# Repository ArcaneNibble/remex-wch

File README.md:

# Project codename "remex"

> remex (noun)
>> a primary or secondary quill feather of the wing of a bird

This is intended to be a "maker"-friendly board for the CH32V307 RISC-V microcontroller from [WCH](https://www.wch-ic.com/). The main selling points are gigabit Ethernet and USB-C including host support.

## Status

There's a vaguely-complete layout, but actual ordering is pending final schematic review as well as further stress-testing of the chosen LiPo charger circuitry.

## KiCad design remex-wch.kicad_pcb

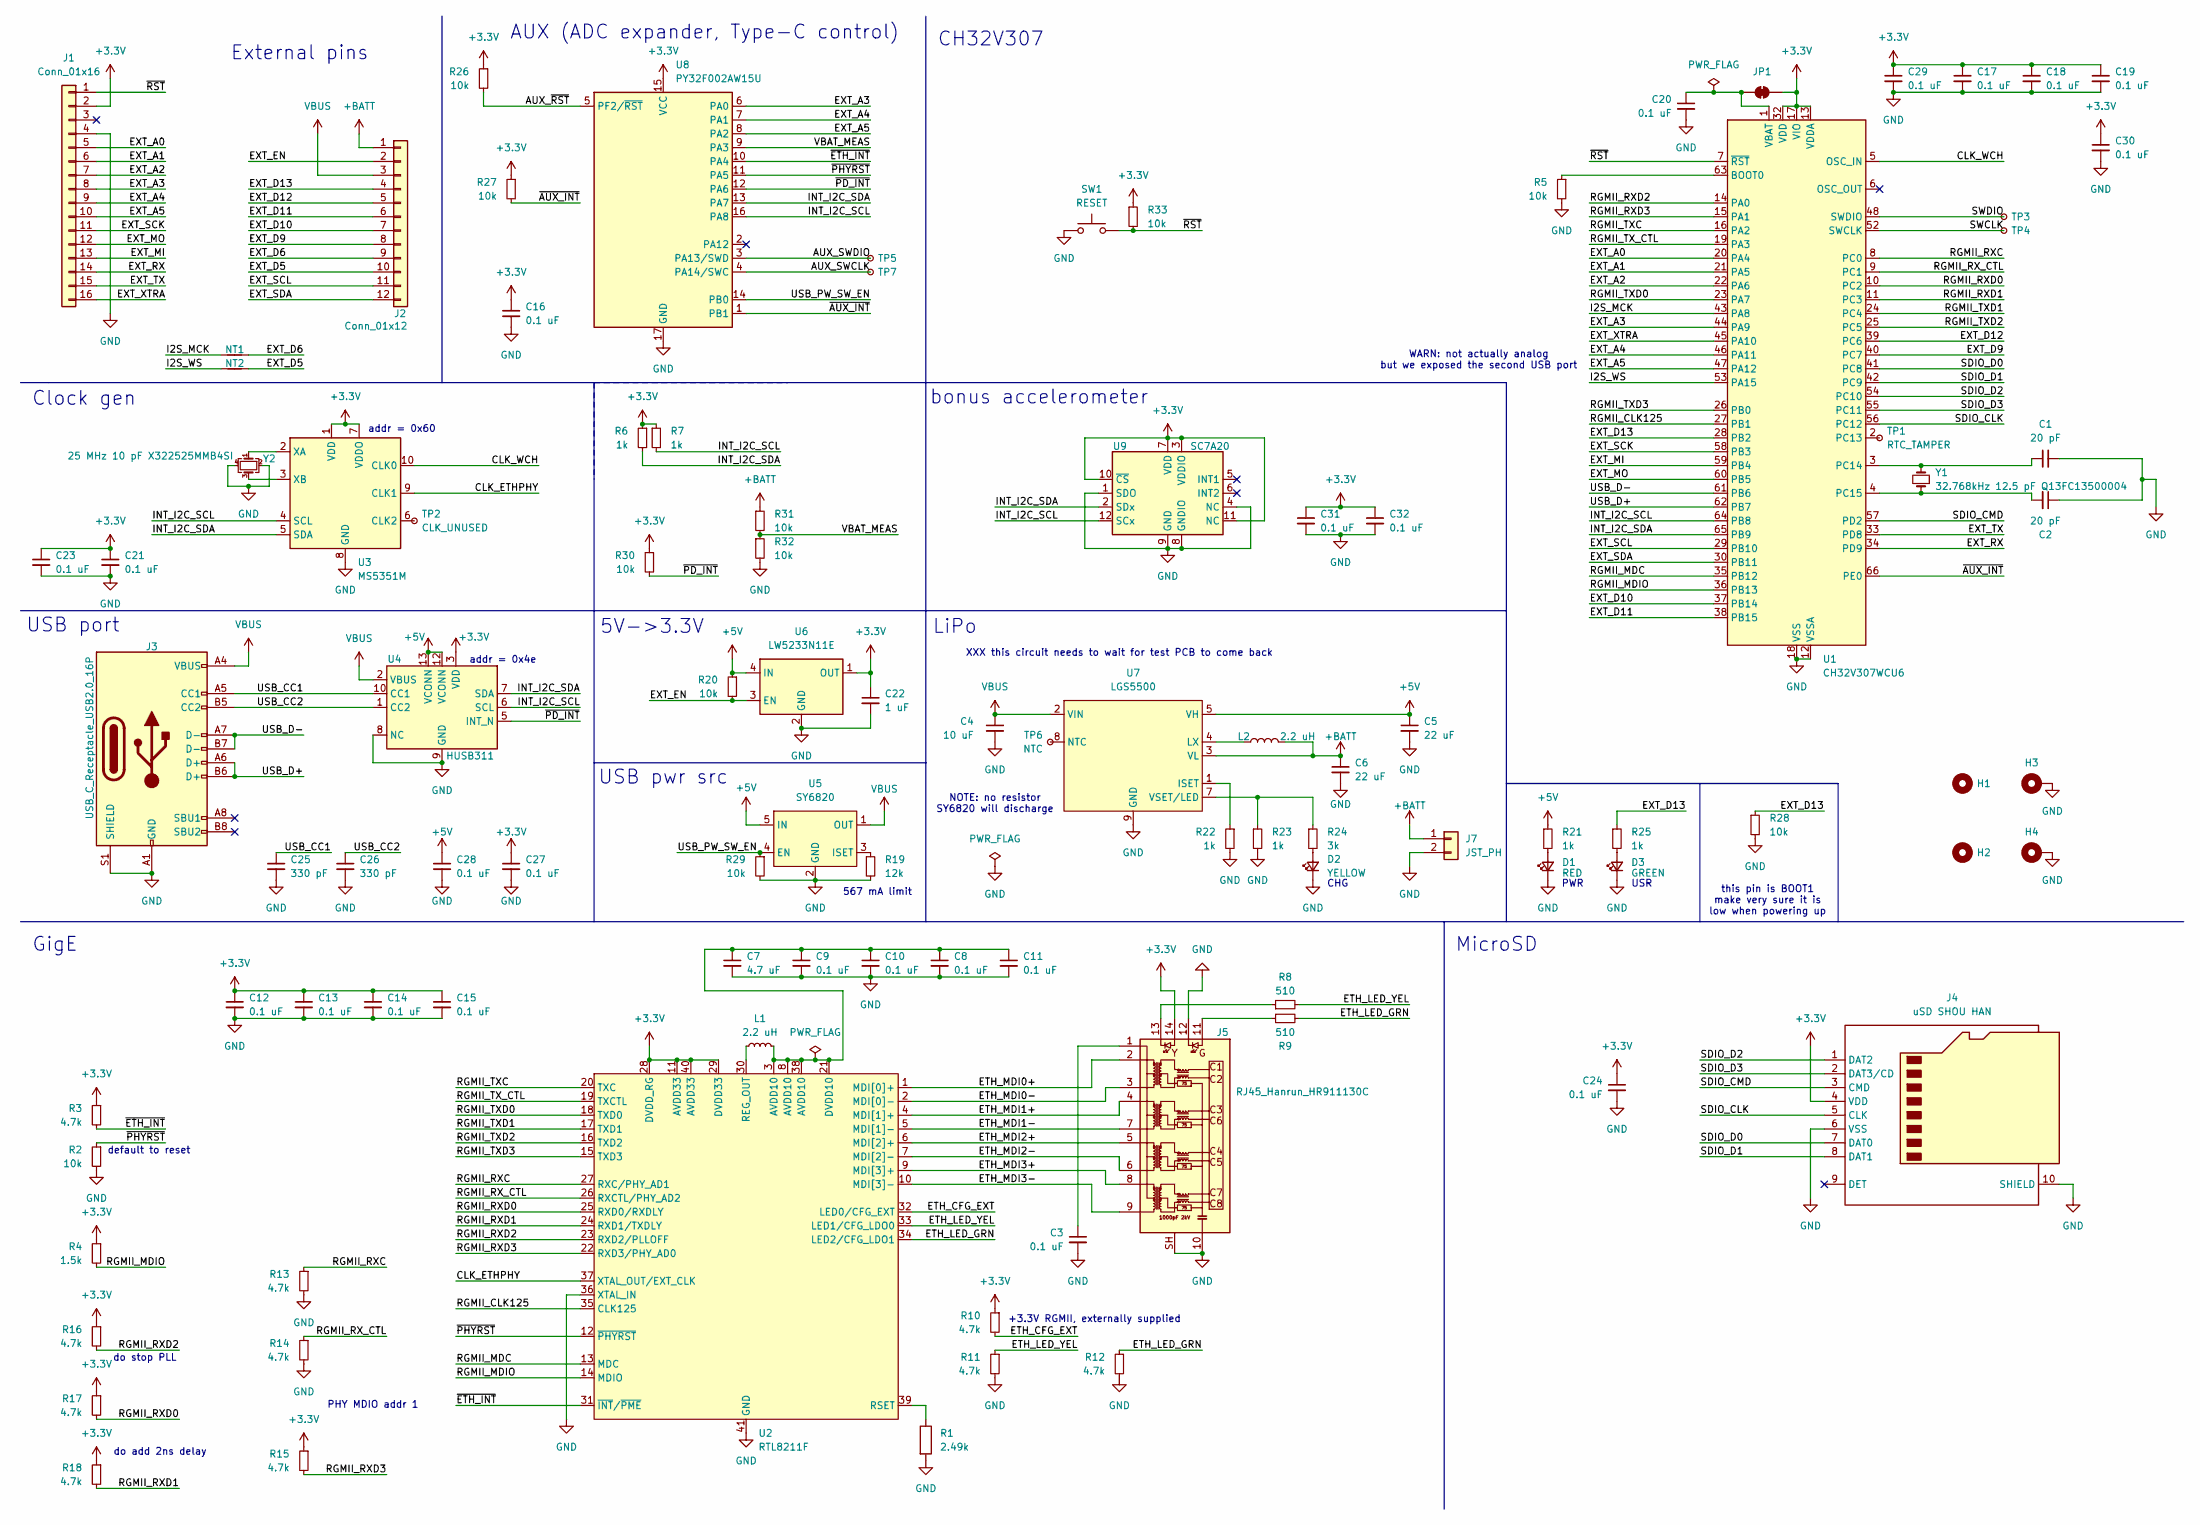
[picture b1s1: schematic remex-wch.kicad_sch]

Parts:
C1, C2: 20 pF; C_0402_1005Metric; LCSC C1554
C3, C8, C9, C10, C11, C12, C13, C14, C15, C16, C17, C18, C19, C20, C21, C23, C24, C27, C28, C29, C30, C31, C32: 0.1 uF; C_0402_1005Metric; LCSC C1525
C4: 10 uF; C_1206_3216Metric; LCSC C13585
C5, C6: 22 uF; C_1206_3216Metric; LCSC C12891
C7: 4.7 uF; C_0603_1608Metric; LCSC C19666
C22: 1 uF; C_0603_1608Metric; LCSC C15849
C25, C26: 330 pF; C_0402_1005Metric; LCSC C13533
D1: RED; LED_0603_1608Metric; LCSC C2286
D2: YELLOW; LED_0603_1608Metric; LCSC C72038
D3: GREEN; LED_0603_1608Metric; LCSC C965804
H1, H2: MountingHole; MountingHole_2.5mm
H3, H4: MountingHole_Pad; MountingHole_2.5mm_Pad
J1: Conn_01x16; PinHeader_1x16_P2.54mm_Vertical
J2: Conn_01x12; PinHeader_1x12_P2.54mm_Vertical
J3: USB_C_Receptacle_USB2.0_16P; USB_C_Receptacle_GCT_USB4105-xx-A_16P_TopMnt_Horizontal; LCSC C2765186
J4: uSD SHOU HAN; microSD_SHOU_HAN_H1.8; LCSC C7529389
J5: RJ45_Hanrun_HR911130C; LCSC C50933
J7: JST_PH; JST_PH_S2B-PH-SM4-TB_1x02-1MP_P2.00mm_Horizontal; LCSC C295747
JP1: VBAT; SolderJumper-2_P1.3mm_Bridged_RoundedPad1.0x1.5mm
L1, L2: 2.2 uH; L_Changjiang_FXL0420; LCSC C167206
NT1, NT2: NetTie_2; nettie_tiny
R1: 2.49k; R_0402_1005Metric; LCSC C145071
R2, R5, R20, R26, R27, R28, R29, R30, R31, R32, R33: 10k; R_0402_1005Metric; LCSC C25744
R3, R10, R11, R12, R13, R14, R15, R16, R17, R18: 4.7k; R_0402_1005Metric; LCSC C25900
R4: 1.5k; R_0402_1005Metric; LCSC C25867
R6, R7, R21, R22, R23, R25: 1k; R_0402_1005Metric; LCSC C11702
R8, R9: 510; R_0402_1005Metric; LCSC C25123
R19: 12k; R_0402_1005Metric; LCSC C25752
R24: 3k; R_0603_1608Metric; LCSC C4211
SW1: RESET; SW_Push_1P1T_XKB_TS-1187A; LCSC C318884
TP1: RTC_TAMPER; TestPoint_Pad_1.0x1.0mm
TP2: CLK_UNUSED; TestPoint_Pad_1.0x1.0mm
TP3: SWDIO; TestPoint_Pad_1.0x1.0mm
TP4: SWCLK; TestPoint_Pad_1.0x1.0mm
TP5: AUX_SWDIO; TestPoint_Pad_1.0x1.0mm
TP6: NTC; TestPoint_Pad_1.0x1.0mm
TP7: AUX_SWCLK; TestPoint_Pad_1.0x1.0mm
U1: CH32V307WCU6; QFN-68-1EP_8x8mm_P0.4mm_EP6.4x6.4mm; LCSC C5142795
U2: RTL8211F; QFN-40-1EP_5x5mm_P0.4mm_EP3.7x3.7mm; LCSC C187932
U3: MS5351M; MSOP-10_3x3mm_P0.5mm; LCSC C1509083
U4: HUSB311; WQFN-14-1EP_2.5x2.5mm_P0.5mm_EP1.4x1.4mm; LCSC C7471922
U5: SY6820; SOT-23-5; LCSC C55136
U6: LW5233N11E; OnSemi_XDFN4-1EP_1.0x1.0mm_EP0.52x0.52mm; LCSC C20630430
U7: LGS5500; SOIC-8-1EP_3.9x4.9mm_P1.27mm_EP2.41x3.3mm; LCSC C5280699
U8: PY32F002AW15U; QFN-16-1EP_3x3mm_P0.5mm_EP1.7x1.7mm; LCSC C5291740
U9: SC7A20; LGA-12_2x2mm_P0.5mm
Y1: 32.768kHz 12.5 pF Q13FC13500004; Crystal_SMD_3215-2Pin_3.2x1.5mm; LCSC C32346
Y2: 25 MHz 10 pF X322525MMB4SI; Crystal_SMD_3225-4Pin_3.2x2.5mm; LCSC C70582

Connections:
+3.3V: C12.1, C13.1, C14.1, C15.1, C16.1, C17.1, C18.1, C19.1, C21.1, C22.1, C23.1, C24.1, C27.1, C29.1, C30.1, C31.1, C32.1, J1.2, J4.4 (VDD), J5.14, JP1.2 (B), R3.1, R4.1, R6.1, R7.1, R10.1, R15.1, R16.1, R17.1, R18.1, R26.1, R27.1, R30.1, R33.1, U1.13 (VDDA), U1.17 (VIO), U1.31 (VIO), U1.32 (VDD), U1.50 (VDD), U1.51 (VIO), U1.67 (VIO), U1.68 (VDD), U2.11 (AVDD33), U2.28 (DVDD_RG), U2.29 (DVDD33), U2.40 (AVDD33), U3.1 (VDD), U3.7 (VDDO), U4.3 (VDD), U4.4 (VDD), U6.1 (OUT), U8.15 (VCC), U9.3 (VDDIO), U9.7 (VDD), U9.10 (~CS), U9.11 (NC)
+5V: C5.1, C28.1, R20.1, R21.1, U4.12 (VCONN), U4.13 (VCONN), U5.5 (IN), U6.4 (IN), U7.5 (VH)
+BATT: C6.1, J2.1, J7.1, L2.2, R31.1, U7.3 (VL)
/AUX_SWCLK: TP7.1, U8.4 (PA14/SWC)
/AUX_SWDIO: TP5.1, U8.3 (PA13/SWD)
/AUX_~RST: R26.2, U8.5 (PF2/~RST)
/CLK_ETHPHY: U2.37 (XTAL_OUT/EXT_CLK), U3.9 (CLK1)
/CLK_WCH: U1.5 (OSC_IN), U3.10 (CLK0)
/ETH_CFG_EXT: R10.2, U2.32 (LED0/CFG_EXT)
/ETH_LED_GRN: R9.2, R12.1, U2.34 (LED2/CFG_LDO1)
/ETH_LED_YEL: R8.2, R11.1, U2.33 (LED1/CFG_LDO0)
/ETH_MDI0+: J5.2 (TD1+), U2.1 (MDI[0]+)
/ETH_MDI0-: J5.3 (TD1-), U2.2 (MDI[0]-)
/ETH_MDI1+: J5.4 (TD2+), U2.4 (MDI[1]+)
/ETH_MDI1-: J5.7 (TD2-), U2.5 (MDI[1]-)
/ETH_MDI2+: J5.5 (TD3+), U2.6 (MDI[2]+)
/ETH_MDI2-: J5.6 (TD3-), U2.7 (MDI[2]-)
/ETH_MDI3+: J5.8 (TD4+), U2.9 (MDI[3]+)
/ETH_MDI3-: J5.9 (TD4-), U2.10 (MDI[3]-)
/EXT_A0: J1.5, U1.20 (PA4)
/EXT_A1: J1.6, U1.21 (PA5)
/EXT_A2: J1.7, U1.22 (PA6)
/EXT_A3: J1.8, U1.44 (PA9), U8.6 (PA0)
/EXT_A4: J1.9, U1.46 (PA11), U8.7 (PA1)
/EXT_A5: J1.10, U1.47 (PA12), U8.8 (PA2)
/EXT_D5: J2.10, NT2.2
/EXT_D6: J2.9, NT1.2
/EXT_D9: J2.8, U1.40 (PC7)
/EXT_D10: J2.7, U1.37 (PB14)
/EXT_D11: J2.6, U1.38 (PB15)
/EXT_D12: J2.5, U1.39 (PC6)
/EXT_D13: J2.4, R25.1, R28.1, U1.28 (PB2)
/EXT_EN: J2.2, R20.2, U6.3 (EN)
/EXT_MI: J1.13, U1.59 (PB4)
/EXT_MO: J1.12, U1.60 (PB5)
/EXT_RX: J1.14, U1.34 (PD9)
/EXT_SCK: J1.11, U1.58 (PB3)
/EXT_SCL: J2.11, U1.29 (PB10)
/EXT_SDA: J2.12, U1.30 (PB11)
/EXT_TX: J1.15, U1.33 (PD8)
/EXT_XTRA: J1.16, U1.45 (PA10)
/I2S_MCK: NT1.1, U1.43 (PA8)
/I2S_WS: NT2.1, U1.53 (PA15)
/INT_I2C_SCL: R7.2, U1.64 (PB8), U3.4 (SCL), U4.6 (SCL), U8.16 (PA8), U9.12 (SCx)
/INT_I2C_SDA: R6.2, U1.65 (PB9), U3.5 (SDA), U4.7 (SDA), U8.13 (PA7), U9.2 (SDx)
/RGMII_CLK125: U1.27 (PB1), U2.35 (CLK125)
/RGMII_MDC: U1.35 (PB12), U2.13 (MDC)
/RGMII_MDIO: R4.2, U1.36 (PB13), U2.14 (MDIO)
/RGMII_RXC: R13.1, U1.8 (PC0), U2.27 (RXC/PHY_AD1)
/RGMII_RXD0: R17.2, U1.10 (PC2), U2.25 (RXD0/RXDLY)
/RGMII_RXD1: R18.2, U1.11 (PC3), U2.24 (RXD1/TXDLY)
/RGMII_RXD2: R16.2, U1.14 (PA0), U2.23 (RXD2/PLLOFF)
/RGMII_RXD3: R15.2, U1.15 (PA1), U2.22 (RXD3/PHY_AD0)
/RGMII_RX_CTL: R14.1, U1.9 (PC1), U2.26 (RXCTL/PHY_AD2)
/RGMII_TXC: U1.16 (PA2), U2.20 (TXC)
/RGMII_TXD0: U1.23 (PA7), U2.18 (TXD0)
/RGMII_TXD1: U1.24 (PC4), U2.17 (TXD1)
/RGMII_TXD2: U1.25 (PC5), U2.16 (TXD2)
/RGMII_TXD3: U1.26 (PB0), U2.15 (TXD3)
/RGMII_TX_CTL: U1.19 (PA3), U2.19 (TXCTL)
/SDIO_CLK: J4.5 (CLK), U1.56 (PC12)
/SDIO_CMD: J4.3 (CMD), U1.57 (PD2)
/SDIO_D0: J4.7 (DAT0), U1.41 (PC8)
/SDIO_D1: J4.8 (DAT1), U1.42 (PC9)
/SDIO_D2: J4.1 (DAT2), U1.54 (PC10)
/SDIO_D3: J4.2 (DAT3/CD), U1.55 (PC11)
/SWCLK: TP4.1, U1.52 (SWCLK)
/SWDIO: TP3.1, U1.48 (SWDIO)
/USB_CC1: C25.1, J3.A5 (CC1), U4.10 (CC1), U4.11 (CC1)
/USB_CC2: C26.1, J3.B5 (CC2), U4.1 (CC2), U4.14 (CC2)
/USB_D+: J3.A6 (D+), J3.B6 (D+), U1.62 (PB7)
/USB_D-: J3.A7 (D-), J3.B7 (D-), U1.61 (PB6)
/USB_PW_SW_EN: R29.1, U5.4 (EN), U8.14 (PB0)
/VBAT_MEAS: R31.2, R32.1, U8.9 (PA3)
/~AUX_INT: R27.2, U1.66 (PE0), U8.1 (PB1)
/~ETH_INT: R3.2, U2.31 (~INT/~PME), U8.10 (PA4)
/~PD_INT: R30.2, U4.5 (INT_N), U8.12 (PA6)
/~PHYRST: R2.1, U2.12 (~PHYRST), U8.11 (PA5)
/~RST: J1.1, R33.2, SW1.2, U1.7 (~RST)
GND: C1.2, C2.1, C3.2, C4.2, C5.2, C6.2, C7.2, C8.2, C9.2, C10.2, C11.2, C12.2, C13.2, C14.2, C15.2, C16.2, C17.2, C18.2, C19.2, C20.2, C21.2, C22.2, C23.2, C24.2, C25.2, C26.2, C27.2, C28.2, C29.2, C30.2, C31.2, C32.2, D1.1 (K), D2.1 (K), D3.1 (K), H3.1, H4.1, J1.4, J3.A1 (GND), J3.A12 (GND), J3.B1 (GND), J3.B12 (GND), J3.S1 (SHIELD), J4.6 (VSS), J4.10 (SHIELD), J5.10 (GND), J5.12, J5.SH, J7.2, R1.2, R2.2, R5.2, R11.2, R12.2, R13.2, R14.2, R19.2, R22.2, R23.2, R28.2, R29.2, R32.2, SW1.1, U1.12 (VSSA), U1.18 (VSS), U1.49 (VSS), U1.69 (VSS), U2.36 (XTAL_IN), U2.41 (GND), U3.8 (GND), U4.8 (NC), U4.9 (GND), U4.15 (GND), U5.2 (GND), U6.2 (GND), U6.5 (GND), U7.9 (GND), U8.17 (GND), U9.1 (SDO), U9.4 (NC), U9.8 (GNDIO), U9.9 (GND), Y2.2, Y2.4
unnamed: D1.2 (A), R21.2
unnamed: D2.2 (A), R24.2
unnamed: D3.2 (A), R25.2
unnamed: C3.1, J5.1 (CT)
unnamed: J5.11, R9.1
unnamed: J5.13, R8.1
unnamed: C20.1, JP1.1 (A), U1.1 (VBAT)
unnamed: R5.1, U1.63 (BOOT0)
unnamed: TP1.1, U1.2 (PC13)
unnamed: C1.1, U1.3 (PC14), Y1.2
unnamed: C2.2, U1.4 (PC15), Y1.1
unnamed: C7.1, C8.1, C9.1, C10.1, C11.1, L1.2, U2.3 (AVDD10), U2.8 (AVDD10), U2.21 (DVDD10), U2.38 (AVDD10)
unnamed: L1.1, U2.30 (REG_OUT)
unnamed: R1.1, U2.39 (RSET)
unnamed: TP2.1, U3.6 (CLK2)
unnamed: U3.2 (XA), Y2.1
unnamed: U3.3 (XB), Y2.3
unnamed: R19.1, U5.3 (ISET)
unnamed: R22.1, U7.1 (ISET)
unnamed: L2.1, U7.4 (LX)
unnamed: TP6.1, U7.8 (NTC)
unnamed: R23.1, R24.1, U7.7 (VSET/LED)
VBUS: C4.1, J2.3, J3.A4 (VBUS), J3.A9 (VBUS), J3.B4 (VBUS), J3.B9 (VBUS), U4.2 (VBUS), U5.1 (OUT), U7.2 (VIN)

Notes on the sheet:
PWR
USB pwr src
USR
5V->3.3V
AUX (ADC expander, Type-C control)
USB port
MicroSD
CH32V307
GigE
default to reset
WARN: not actually analog but we exposed the second USB port
NOTE: no resistor SY6820 will discharge
LiPo
addr = 0x60
Clock gen
567 mA limit
CHG
External pins
this pin is BOOT1 make very sure it is low when powering up
do stop PLL
+3.3V RGMII, externally supplied
PHY MDIO addr 1
addr = 0x4e
bonus accelerometer
do add 2ns delay
XXX this circuit needs to wait for test PCB to come back

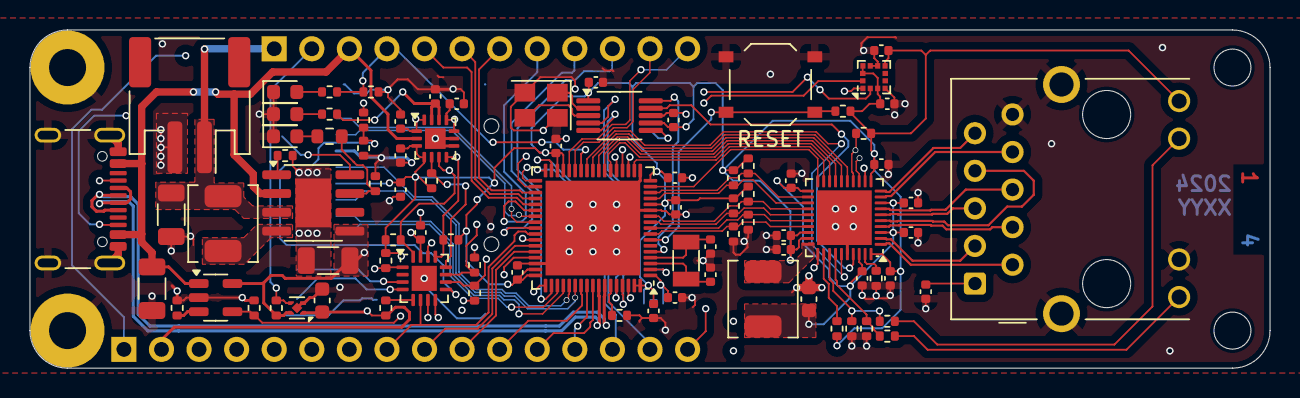
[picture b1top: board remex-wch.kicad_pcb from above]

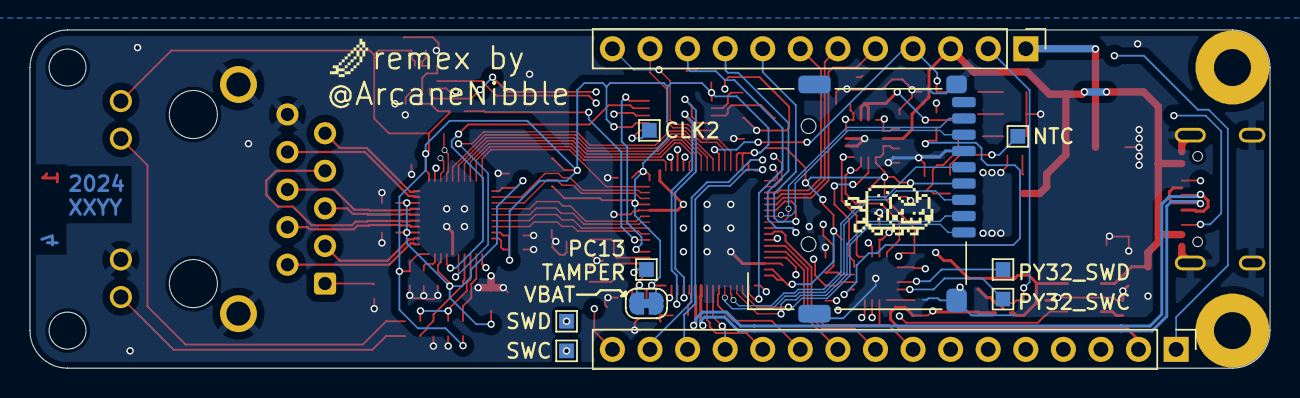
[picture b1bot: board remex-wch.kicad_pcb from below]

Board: 4 copper layers, 83.8 x 22.9 mm, 102 parts (13 on the bottom side), 103 nets.

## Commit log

2024-08-19 Initial pin allocation for MCU
2024-08-19 USB port; assign BOM data now
2024-08-19 Shuffle pins to get an internal I2C bus
2024-08-19 initial eth phy
2024-08-19 microsd socket
2024-08-19 clock generator
2024-08-19 ethernet magjack; straps
2024-08-19 rearrange positions
2024-08-19 misc
2024-08-19 add usb typec controller
2024-08-20 Add TBD LiPo circuitry
2024-08-20 py32 as io/adc expander and type-c supervisor
2024-08-20 tidy up a bit
2024-08-20 ch32v boot1
2024-08-20 some bom data filling in
2024-08-20 pile of capacitors
2024-08-20 copy/add easy footprints
2024-08-20 add magjack footprint
2024-08-20 add microsd footprint
2024-08-20 rough positioning of parts on pcb
2024-08-20 fix uSD courtyard
2024-08-20 add reset button
2024-08-29 optimistic parts packing closer together
2024-08-29 not-good-approx test routing
2024-08-29 setup; tweaks
2024-08-29 more board setup
2024-08-29 better initial attempt at all the hard signals
2024-08-29 work on power section
2024-08-29 work on usb c mgmt section
2024-08-29 work on clock chip
2024-08-29 everything connected
2024-08-29 clean up fab layers
2024-08-29 correct 10pf crystal
2024-08-29 hopefully fix nettie
2024-08-29 fix some part values
2024-08-29 silk, debug, misc
2024-08-29 silk art
2024-08-29 simple trace nudging
2024-08-29 add resest label on top silk
2024-08-29 misc poke
2024-08-29 dim notes
2024-09-03 Add some DRC exclusions
2024-09-03 Add README
2024-09-06 small tweaks
2024-09-06 more tweaks; prepare for adding accel
2024-09-06 add bonus accel
2024-09-06 more tweaks
